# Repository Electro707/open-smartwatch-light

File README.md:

# Open-Smartwatch KiCAD files, Electro707's Fork

Repo Electro707's fork of the Open-Smartwatch project. You should be in the `e707` branch.

## My Changes
Here are some changes that I plan on doing to this design:
- Replace the battery charger and power mux combo with an integrated PowerPath TI charger IC (BQ24230RGT)
- Replace the module with an ESP32-PICO-MINI-02
- Replace the connector with a TypeC
- Replace the RTC with a smaller package one (RV-8523-C3)
- Added a 3D compass/accelerometer/gyroscope IC
- Added a temperature/humidity/pressure sensor (BME280)

## Tools

To view/modify the files from this repository, install KiCAD from: [https://kicad.org](https://kicad.org). 
__Must use the nightly version of KiCAD, bonus points if you build it from source__

Also, add the following Symbol/Footprint library to KiCAD: [https://github.com/Open-Smartwatch/Kicad-Libraries](https://github.com/Open-Smartwatch/Kicad-Libraries)

## Schematic (May not be updated to this version)

## Plots (May not be updated to this version)

## BOM (May not be updated to this version)

See: [https://htmlpreview.github.io/?https://github.com/Open-Smartwatch/open-smartwatch-light/blob/main/docs/bom/osw-light-ibom.html](https://htmlpreview.github.io/?https://github.com/Open-Smartwatch/open-smartwatch-light/blob/main/docs/bom/osw-light-ibom.html)

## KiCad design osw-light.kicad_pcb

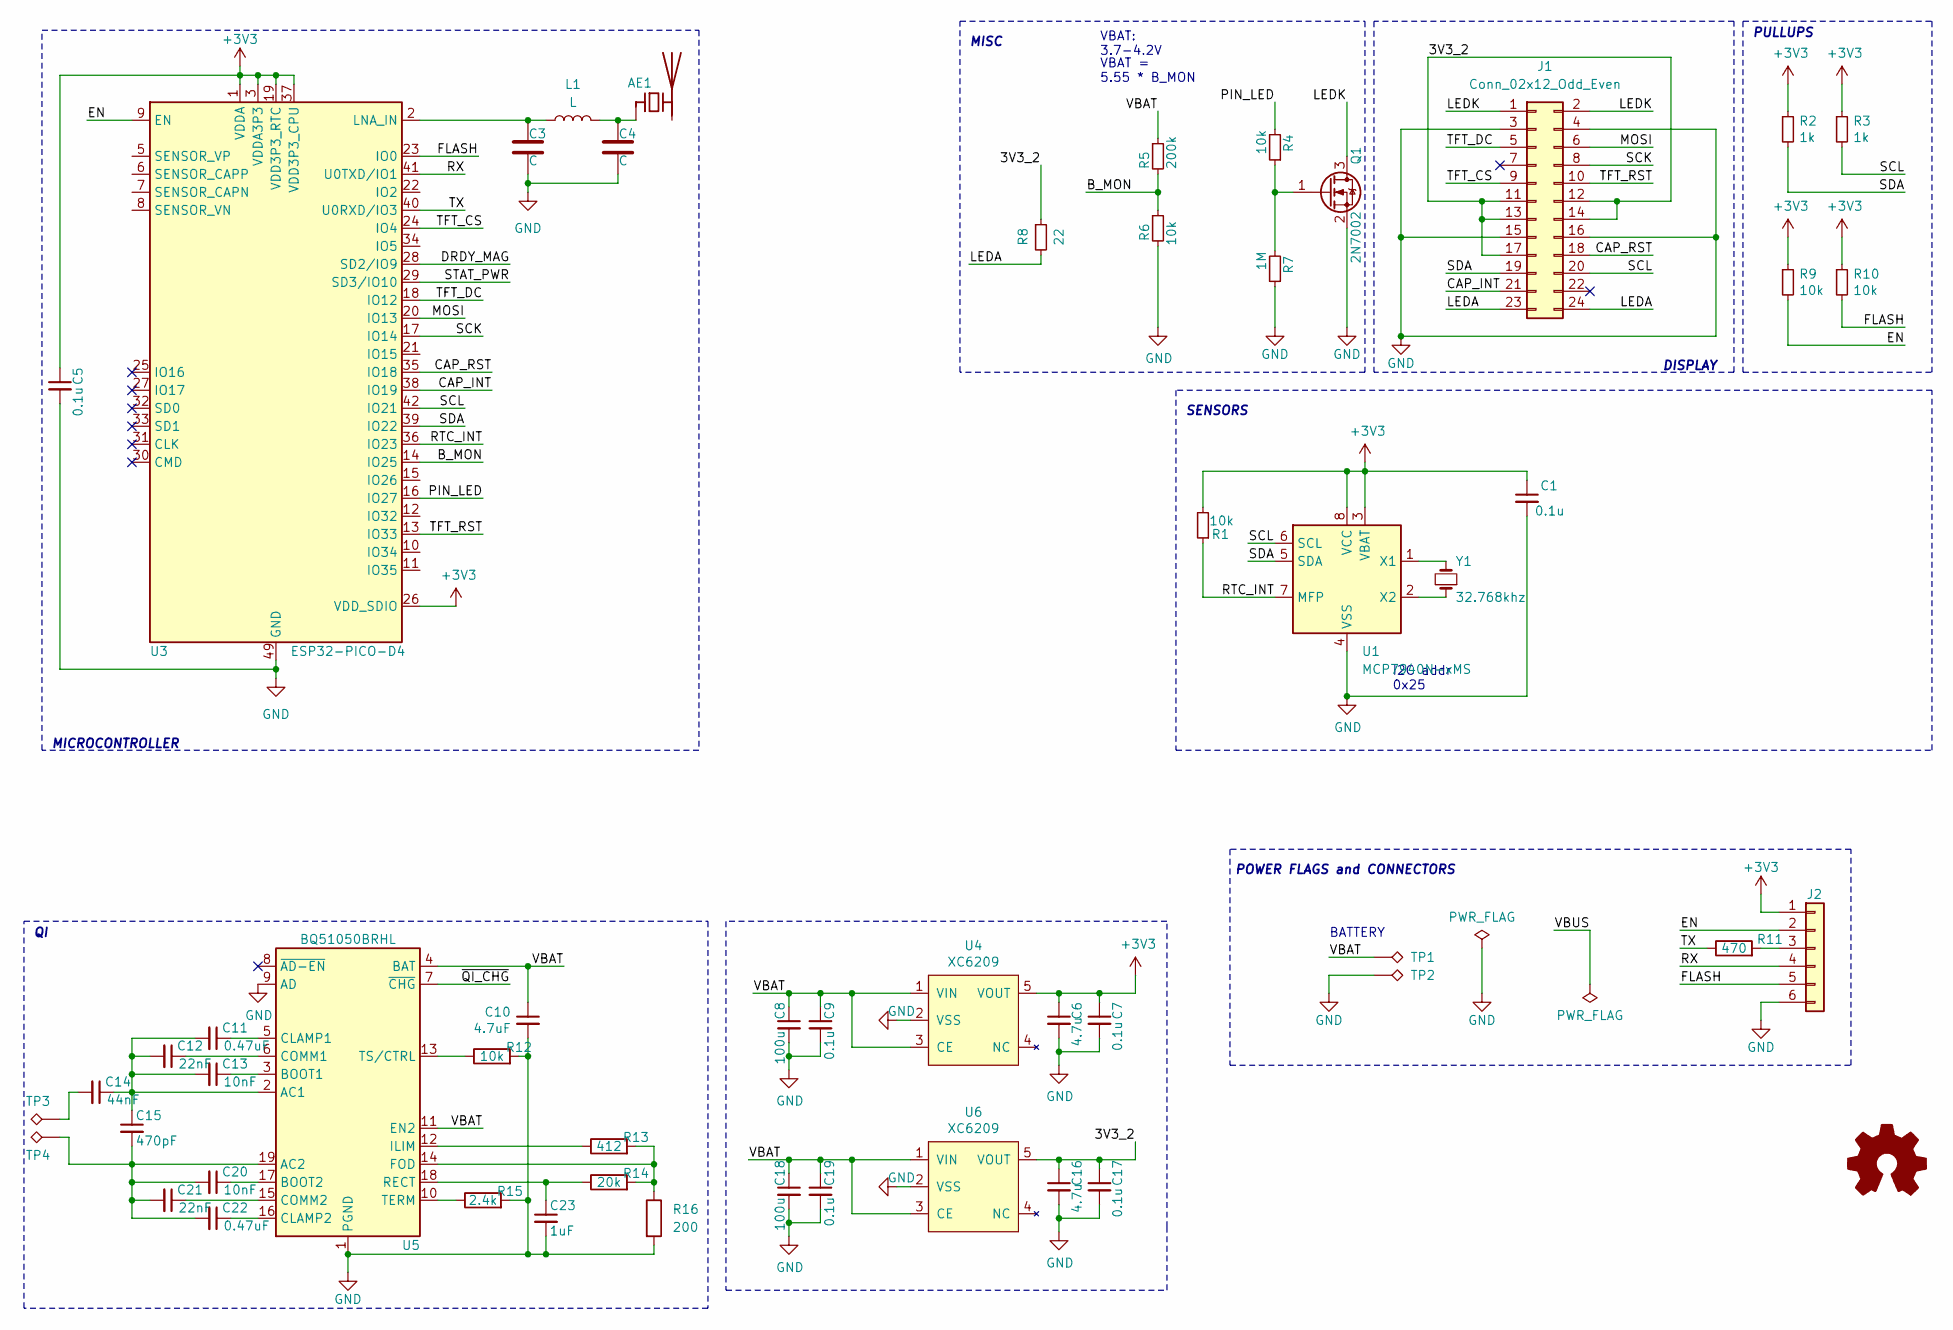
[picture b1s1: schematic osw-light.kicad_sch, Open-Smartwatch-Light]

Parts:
AE1: Antenna_Chip; Johanson_2450AT43F0100
C1, C5, C7, C9, C17, C19: 0.1u; C_0603_1608Metric
C3, C4: C; C_0603_1608Metric
C6, C16: 4.7u; C_0805_2012Metric
C8, C18: 100u; C_1206_3216Metric
C10: 4.7uF; C_0805_2012Metric
C11, C22: 0.47uF; C_0603_1608Metric
C12, C21: 22nF; C_0603_1608Metric
C13, C20: 10nF; C_0603_1608Metric
C14: 44nF; C_0805_2012Metric
C15: 470pF; C_0805_2012Metric
C23: 1uF; C_0603_1608Metric
J1: Conn_02x12_Odd_Even; DisplayFlexConnector
J2: Conn_01x06; Tag-Connect_TC2030-IDC-NL_2x03_P1.27mm_Vertical
L1: L; L_0805_2012Metric_Pad1.05x1.20mm_HandSolder
Q1: 2N7002; SOT-23
R1, R4, R6, R9, R10, R12: 10k; R_0603_1608Metric
R2, R3: 1k; R_0603_1608Metric
R5: 200k; R_0603_1608Metric
R7: 1M; R_0603_1608Metric
R8: 22; R_0603_1608Metric
R11: 470; R_0603_1608Metric
R13: 412; R_0603_1608Metric
R14: 20k; R_0603_1608Metric
R15: 2.4k; R_0603_1608Metric
R16: 200; R_0603_1608Metric
TP1, TP2, TP3, TP4: BATT-VCC; TestPoint_Pad_3.0x3.0mm
U1: MCP7940N-xMS; MSOP-8_3x3mm_P0.65mm
U3: ESP32-PICO-D4; QFN-48-1EP_7x7mm_P0.5mm_EP5.3x5.3mm
U4, U6: XC6209; SOT-23-5
U5: BQ51050BRHL; Texas_VQFN-RHL-20
Y1: 32.768khz; Crystal_SMD_3215-2Pin_3.2x1.5mm

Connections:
+3V3: C1.1, C5.1, C6.1, C7.1, J2.1, R1.2, R2.1, R3.1, R9.1, R10.1, U1.3 (VBAT), U1.8 (VCC), U3.1 (VDDA), U3.3 (VDDA3P3), U3.4 (VDDA3P3), U3.19 (VDD3P3_RTC), U3.26 (VDD_SDIO), U3.37 (VDD3P3_CPU), U3.43 (VDDA), U3.46 (VDDA), U4.5 (VOUT)
/3V3_2: C16.1, C17.1, J1.11, J1.12, J1.13, J1.14, J1.17, R8.1, U6.5 (VOUT)
/B_MON: R5.2, R6.1, U3.14 (IO25)
/CAP_INT: J1.21, U3.38 (IO19)
/CAP_RST: J1.18, U3.35 (IO18)
/DRDY_MAG: U3.28 (SD2/IO9)
/EN: J2.2, R9.2, U3.9 (EN)
/FLASH: J2.5, R10.2, U3.23 (IO0)
/LEDA: J1.23, J1.24, R8.2
/LEDK: J1.1, J1.2, Q1.3 (D)
/MOSI: J1.6, U3.20 (IO13)
/PIN_LED: R4.2, U3.16 (IO27)
/RTC_INT: R1.1, U1.7 (MFP), U3.36 (IO23)
/RX: J2.4, U3.41 (U0TXD/IO1)
/SCK: J1.8, U3.17 (IO14)
/SCL: J1.20, R3.2, U1.6 (SCL), U3.42 (IO21)
/SDA: J1.19, R2.2, U1.5 (SDA), U3.39 (IO22)
/STAT_PWR: U3.29 (SD3/IO10)
/TFT_CS: J1.9, U3.24 (IO4)
/TFT_DC: J1.5, U3.18 (IO12)
/TFT_RST: J1.10, U3.13 (IO33)
/TX: R11.1, U3.40 (U0RXD/IO3)
/VBAT: C8.1, C9.1, C10.1, C18.1, C19.1, R5.1, TP1.1, U4.1 (VIN), U4.3 (CE), U5.4 (BAT), U5.11 (EN2), U6.1 (VIN), U6.3 (CE)
/~QI_CHG: U5.7 (~CHG)
GND: C1.2, C3.2, C4.2, C5.2, C6.2, C7.2, C8.2, C9.2, C10.2, C16.2, C17.2, C18.2, C19.2, C23.2, J1.3, J1.4, J1.15, J1.16, J2.6, Q1.2 (S), R6.2, R7.1, R12.2, R15.2, R16.2, TP2.1, U1.4 (VSS), U3.49 (GND), U4.2 (VSS), U5.1 (PGND), U5.9 (AD), U5.20 (PGND), U5.21 (PGND), U6.2 (VSS)
unnamed: AE1.1 (FEED), C4.1, L1.2
unnamed: C3.1, L1.1, U3.2 (LNA_IN)
unnamed: C11.1, U5.5 (CLAMP1)
unnamed: C11.2, C12.2, C13.2, C14.1, C15.1, U5.2 (AC1)
unnamed: C12.1, U5.6 (COMM1)
unnamed: C13.1, U5.3 (BOOT1)
unnamed: C14.2, TP3.1
unnamed: C15.2, C20.2, C21.2, C22.2, TP4.1, U5.19 (AC2)
unnamed: C20.1, U5.17 (BOOT2)
unnamed: C21.1, U5.15 (COMM2)
unnamed: C22.1, U5.16 (CLAMP2)
unnamed: C23.1, R14.1, U5.18 (RECT)
unnamed: J2.3, R11.2
unnamed: Q1.1 (G), R4.1, R7.2
unnamed: R12.1, U5.13 (TS/CTRL)
unnamed: R13.1, U5.12 (ILIM)
unnamed: R13.2, R14.2, R16.1, U5.14 (FOD)
unnamed: R15.1, U5.10 (TERM)
unnamed: U1.1 (X1), Y1.2
unnamed: U1.2 (X2), Y1.1

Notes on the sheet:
VBAT: 3.7-4.2V
I2C addr 0x25
MISC
VBAT = 5.55 * B_MON
MICROCONTROLLER
DISPLAY
BATTERY
PULLUPS
SENSORS
POWER FLAGS and CONNECTORS

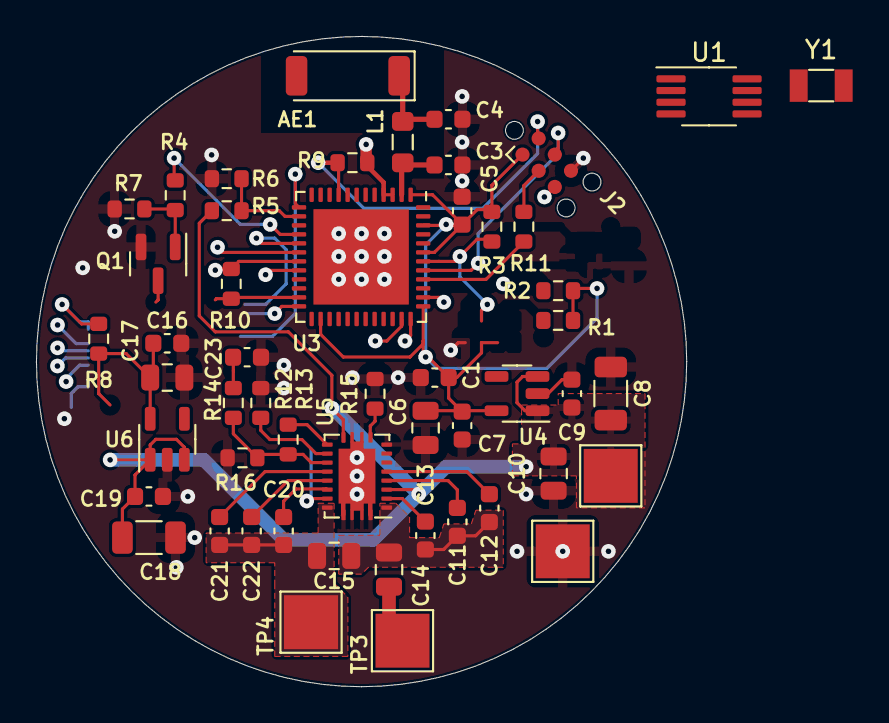
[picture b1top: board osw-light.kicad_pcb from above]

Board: 4 copper layers, 36.1 x 36.1 mm, 53 parts (1 on the bottom side), 42 nets.

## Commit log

2021-04-14 Starting to add my modifications
2021-04-15 Finalized layout
2021-04-16 Started working on LoRa version/changes
2021-04-16 Changed README.md for this branch
2021-04-18 Layed out board. Changed a duplicate sensor for a temperature one
2021-04-18 Fixed silkscreens. Replaced duplicate sensor with temperature sensor
2021-04-19 Another commit. Removed gerbers as part of a git release
2021-04-20 Changed switch to proper one
2021-05-16 Added a TODO list for a potential Rev2.0
2021-08-03 Started work on a Rev2 of this fork
2021-08-07 Initial traces for Rev2
2021-08-10 Near finished with Rev2 Design
2021-11-23 Added dormant file from my local git
2021-12-26 Started work on a Rev3
